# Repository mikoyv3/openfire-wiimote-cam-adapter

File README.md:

# OpenFIRE (I2C) DIY Wiimote IR Camera PCB

<p align="center">
  <table align="center">
    <tr>
      <td align="center"><b>Variant Layout</b></td>
      <td align="center"><b>PCB Front View</b></td>
      <td align="center"><b>PCB Back View</b></td>
      <td align="center"><b>OpenFIRE Official Wiring Diagram & Camera Pin Labels</b></td>
    </tr>
    <tr>
      <td align="center" valign="middle"><b>JST PH 2.0</b><br>(1/4W Resistors)<br>PCB Size<br>13*30.1 mm</td>
      <td align="center" valign="middle">
        
      </td>
      <td align="center" valign="middle">
        
      </td>
      <td align="center" valign="middle" rowspan="4">
        
      </td>
    </tr>
    <tr>
      <td align="center" valign="middle" colspan="3">
        <b>🟣 <a href="https://oshpark.com/shared_projects/DqOJEs91" target="_blank">Order JST PH 2.0 Board from OSH Park (0.8mm thickness)</a></b>
      </td>
    </tr>
  </table>
</p>

<p align="center">
  <table align="center">
    <tr>
      <td align="center"><b>Variant Layout</b></td>
      <td align="center"><b>PCB Front View</b></td>
      <td align="center"><b>PCB Back View</b></td>
      <td align="center"><b>OpenFIRE Unofficial Wiring Diagram</b></td>
    </tr>
    <tr>
      <td align="center" valign="middle"><b>JST PH 2.0</b><br>(1/4W Resistors<br><b> and 0.1µF Capacitor)</b><br>PCB Size<br>13*30.1 mm</td>
      <td align="center" valign="middle">
        
      </td>
      <td align="center" valign="middle">
        
      </td>
      <td align="center" valign="middle">
        
      </td>
    </tr>
    <tr>
      <td align="center" valign="middle"><b>Design Purpose & Deviation Notes</b></td>
      <td align="center" valign="middle" colspan="3" align="left">
     Discussions from OpenFIRE Discord suggested that adding a decoupling ceramic capacitor on the camera module's power rail is best practice to stabilize voltage delivery and minimize potential noise. There is an active documentation change request to update the official OpenFIRE schematic guidelines accordingly (<a href="https://github.com/TeamOpenFIRE/OpenFIRE-App/issues/120" target="_blank">Issue #120</a>). In the meantime, this layout provides that feature as an option. Keep in mind that the official one has no reported issues and is perfectly fine. 
      </td>
    </tr>
    <tr>
      <td align="center" valign="middle" colspan="4">
        <b>🟣 <a href="https://oshpark.com/shared_projects/3LxfKNea" target="_blank">Order JST PH 2.0 Unofficial Board from OSH Park (0.8mm thickness)</a></b>
      </td>
    </tr>
  </table>
</p>

<kbd>
<p align="center">
🛑⚠️ Gun4IR/OpenFIRE/Blamcon DIY: The Easy, Pre-Assembled JLCPCB Method ⚠️🛑 <br>  (ALTERNATIVE / PLAN B / OPTION 2)
</p>

If you need the easiest and fastest way to build your IR camera pcb. By leveraging JLCPCB’s PCBA (PCB Assembly) service, you receive a nearly complete, surface-mount-assembled board straight from the factory.

You do not need to hand-solder tiny surface-mount components. The factory handles 99% of the work. Your only job is to hand-solder the Wii IR camera (and standard through-hole connectors like the Pro Micro headers or pins) once the board arrives.

For step-by-step instructions on how to configure your fabrication settings, upload your files, and complete your order, follow my detailed [JLCPCB PCBA Ordering Guide](https://github.com/mikoyv3/openfire-wiimote-cam-adapter/blob/main/JLCPCB/PCBA_Ordering.md).

* **Base Board Design:** [eatnooM PixArt Sensor Adapter (Release v1.3)](https://github.com/eatnooM/pixart-sensor-adapter/releases/tag/v1.3)
* **Required (not included):** [JST MX 1.25mm Wire Cable Connector (4 Pin)](https://www.aliexpress.com/item/1005007277110532.html)
* **Preferred Fabricator:** [JLCPCB](https://jlcpcb.com/)

</kbd>

## 🛠️ Assets
[Download](https://github.com/mikoyv3/openfire-wiimote-cam-adapter/releases) the corresponding Gerber zip files depending on your preferred connector type and size layout constraint.

---

## 🎗️ Credits & Attribution
This hardware design is an evolutionary community effort built upon the foundations laid by local open-source creators:
* **Circuit Architecture:** Derived from and heavily based on the open-source layout by **[@eatnooM](https://github.com/eatnooM)** ([eatnooM/pixart-sensor-adapter](https://github.com/eatnooM/pixart-sensor-adapter)).
* **3D Enclosure Development:** Enclosure integrations, printing assets, and specialized repository files are hosted, maintained, and credited to **[@slikvik55](https://github.com/slikvik55)** ([slikvik55/Lightgun3DParts](https://github.com/slikvik55/Lightgun3DParts)).
* **Assembly Tools:** Special thanks to **Gzus348** for creating the original camera jig design that makes sensor alignment straightforward.

---

## 🚀 Key Features

* **Beginner-Friendly Through-Hole Resistors:** Uses through-hole resistors (4.7kΩ) for easy hand-soldering and a slim profile.
* **Official Hardware Guide Aligned:** The trace layout is designed directly from the "DIY Wiimote Conversion (Using Clock Pin)" schematic on **page 4** of the official **[OpenFIRE-Hardware-Guide_1.3.pdf](https://openfirelightgun.org/wp-content/uploads/2026/10/OpenFIRE-Hardware-Guide_1.3.pdf)** manual.
* **Optional 5-Pin JST Connector:** Physical JST socket will fit the barrel shell and should be inserted from the back and the IR camera cover last. 
* **Enclosure-Ready Geometry:** Formatted specifically to seat right into RetroMidget's Wiimote camera housing using standard dimensions from @slikvik55's Lightgun3DParts repository.
* **Zero Onboard Crystal Needed:** Relies on OpenFIRE's native pin-generated clock (`CLK`), omitting external oscillators.
* **Direct 3.3V Power Line:** Streamlined 3.3V power path supplied directly by a Raspberry Pi Pico.

---

## 📐 Preparation, Assembly, 3D Shell Compatibility & Enclosure Notes

Tailored for **RetroMidget's Wiimote Camera Enclosure** using assets from [@slikvik55's Lightgun3DParts Repository](https://github.com/slikvik55/Lightgun3DParts/tree/main/WiiCamEnclosure):
* 📥 **Main Shell:** [WiiCamEnclosure Barrel STL](https://github.com/mikoyv3/openfire-wiimote-cam-adapter/blob/main/stl/Barrel.stl)
* 📥 **Internal Mount:** [Camera Holder (JST) STL](https://github.com/mikoyv3/openfire-wiimote-cam-adapter/blob/main/stl/CamHolder-jst.stl)
* 📥 **Assembly Tool:** [Soldering Alignment Jig (JST) STL from **Gzus348**](https://github.com/mikoyv3/openfire-wiimote-cam-adapter/blob/main/stl/JIG-JST.stl)

### Assembly & Soldering Tips:
* **Wii IR Plastic Placement:** Remember to salvage the original dark translucent **Wii IR plastic screen** from the front of the donor Wii remote shell. It needs to be **cut to fit** cleanly inside the [Camera Holder](https://github.com/mikoyv3/openfire-wiimote-cam-adapter/blob/main/stl/CamHolder-jst.stl) piece during assembly. This lens acts as an essential optical filter that blocks ambient room light, ensuring the camera tracks only pure infrared lightbar signals.
* **Flux Recommendation:** Use high-quality flux like **Chip Quik SMD291** when soldering the Wii IR camera onto the PCB.
* **Soldering Assist:** Print and use the [Soldering Alignment Jig](https://github.com/mikoyv3/openfire-wiimote-cam-adapter/blob/main/stl/JIG-JST.stl) to maintain flush alignment.

### PCB IR edge prep:

<p align="center">
  <table align="center">
    <tr>
      <td align="center"><b>PCB Before</b></td>
      <td align="center"><b>PCB After</b></td>
      <td align="center"><b>Tool (Nail File)</b></td>
    </tr>
    <tr>
      <td align="center" valign="middle">
        
      </td>
      <td align="center" valign="middle">
        
      </td>
      <td align="center" valign="middle">
        
      </td>      
  </table>
</p>

* **⚠️🚨❗ <ins>To do this safely</ins> ❗🚨⚠️** Because PCB material contains woven fiberglass, wear gloves, safety glasses, and an N95 face mask to prevent skin and eye irritation and avoid breathing in fine glass dust. Afterward, wipe the board and your work area with a damp cloth or isopropyl alcohol instead of blowing the dust away. Finally, throw away the used nail file, face mask, and cleaning cloth.
* Filing the PCB edge removes rough manufacturing burrs so the Wii IR camera sits flat and its 8 pins align directly with the solder pads.
* Lightly file the inner cutout edge until it is smooth and straight, stopping just before you touch the dark copper solder pads. 
* A cheap dollar-store nail file works well for this task because its thin profile fits easily into the small PCB cutout and its fine grit gently levels the fiberglass edge without damaging the nearby solder pads.

---

## ✅ Testing and Validation:

* **OpenFIRE Official DIY Camera Wiring**<br>

* **OpenFIRE Unofficial DIY Camera Wiring**<br>
  
<br>

* **Eatnoom v1.3 IR camera PCBs using JLCPCB’s PCBA service**<br>
    
<br>

---

## 🛠 Ordering & Assembly Instructions

### PCB Ordering Specifications
⚠️ **CRITICAL FABRICATION NOTE:** When ordering from fabricators like **JLCPCB (Preferred)**, PCBWay, or OSH Park, you **MUST specify a PCB Thickness of 0.8mm**, standard 1.6mm thickness boards are too thick and will not go through the Jig and Barrel!

* **Layers:** 2-layer
* **Thickness:** 0.8 mm (Do not use standard 1.6mm!)
* **Surface Finish:** HASL
  
### Bill of Materials (BOM)
* **U1:** Salvaged Nintendo Wiimote IR Camera Sensor
* **R1:** 4.7kΩ Through-Hole Metal Film Resistor 
* **R2:** 4.7kΩ Through-Hole Metal Film Resistor
* **C1:** 100NF 0.1uF Through-Hole Monolithic Ceramic Capacitor (Unofficial)
* **JST (Optional):** 5-pin JST (PH 2.0) Bent Pin Connector (GND, VCC, SDA, SCL, CLK) and Cable

## 📌 Wiring Diagram Alignment

Ensure the Raspberry Pi Pico pinouts map directly to the corresponding board output lines. While you can configure your own pinouts in firmware, here is the recommended standard layout:

* **GND:** Connect board **GND** ➔ Raspberry Pi Pico **GND** (Any ground pin)
* **CLK:** Connect board **CLK** ➔ Raspberry Pi Pico **GP22** <br>
  *(💡 Note: GP22 is the suggested pin-out. Clock pin will need to be set in the OpenFIRE application).*
* **VCC:** Connect board **VCC** ➔ Raspberry Pi Pico **3V3 OUT**
* **SDA:** Connect board **SDA** ➔ Raspberry Pi Pico **GP20**
* **SCL:** Connect board **SCL** ➔ Raspberry Pi Pico **GP21**

---

## 📜 License
Following the upstream license of the original work, this project is licensed under the **Creative Commons Attribution-ShareAlike 4.0 International License (CC BY-SA 4.0)**. You are free to share and adapt this work as long as you provide appropriate attribution and distribute your contributions under the same license.

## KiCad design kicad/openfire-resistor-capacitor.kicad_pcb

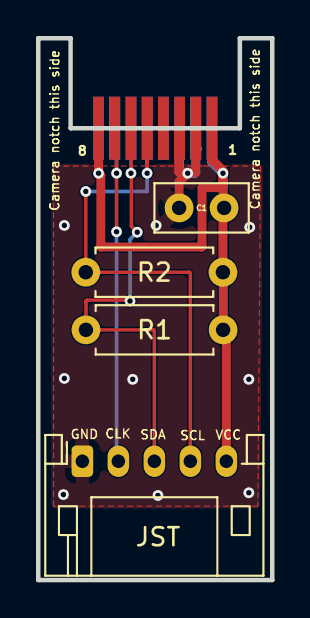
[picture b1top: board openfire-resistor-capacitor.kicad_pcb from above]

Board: 2 copper layers, 13.0 x 30.1 mm, 4 parts (0 on the bottom side), 4 nets.

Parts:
C1: C_Disc_D5.0mm_W2.5mm_P2.50mm
JST: JST_PH_S5B-PH-K_1x05_P2.00mm_Horizontal
R1, R2: R_Axial_DIN0207_L6.3mm_D2.5mm_P7.62mm_Horizontal

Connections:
GND: C1.1, JST.1
SCL: JST.4, R2.1
SDA: JST.3, R1.1
VCC: C1.2, JST.5, R1.2, R2.2
